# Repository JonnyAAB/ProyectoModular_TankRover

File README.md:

# ProyectoModular_TankRover
Este es un repositorio de un proyecto que ya está avanzado

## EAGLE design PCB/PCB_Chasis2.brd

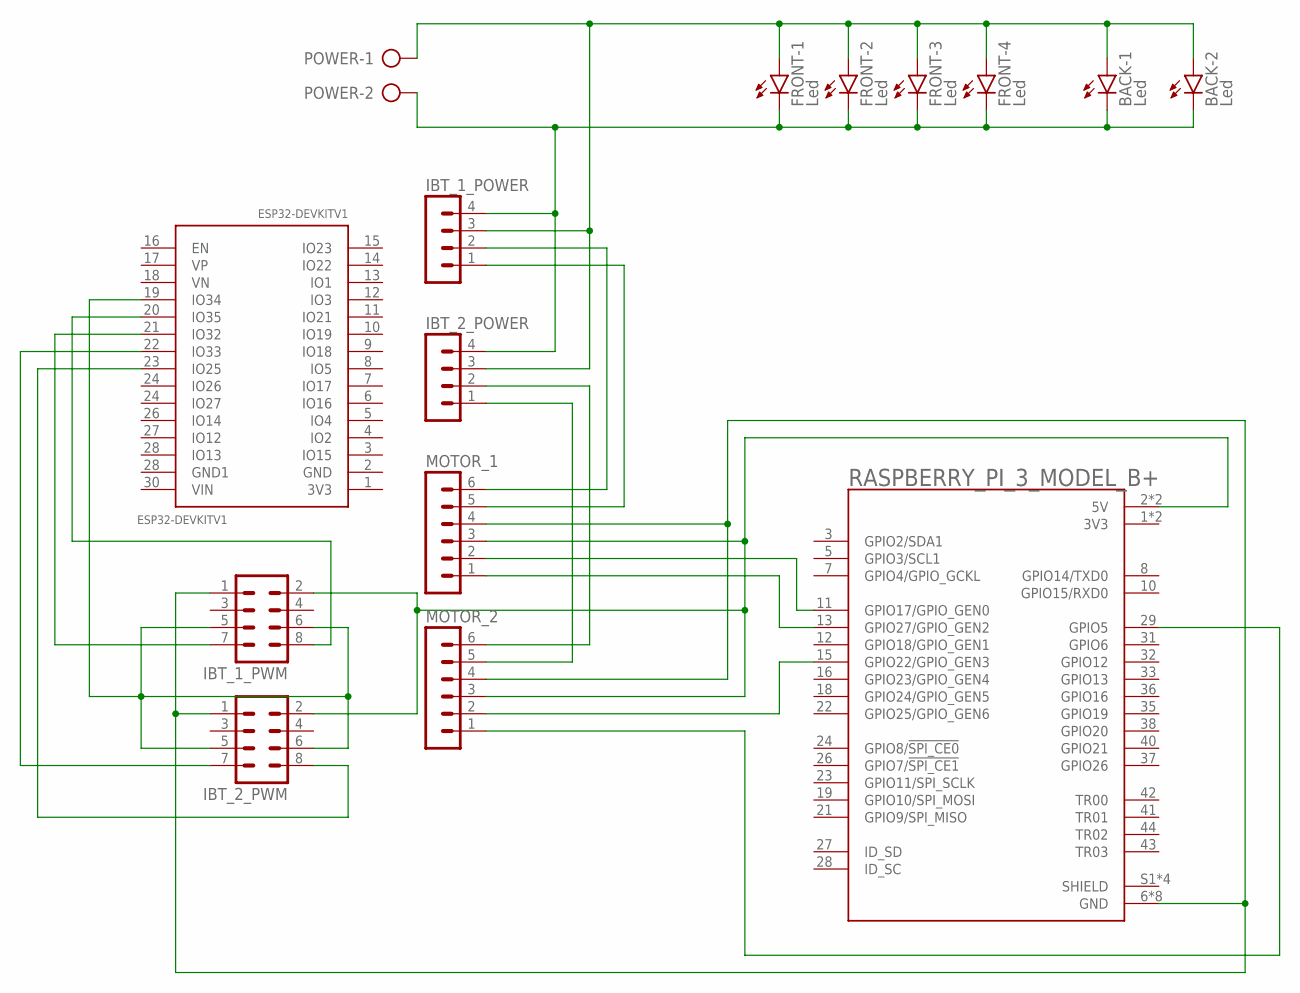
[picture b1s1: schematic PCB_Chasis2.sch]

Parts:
BACK: Led; LZR182
ESP32-DEVKITV1: ESP32DEVKITV1; ESP32-DEVKITV1
FRONT: Led; LZR184
IBT_1_POWER, IBT_2_POWER: MA04-1
IBT_1_PWM, IBT_2_PWM: MA04-2
MOTOR_1, MOTOR_2: MA06-1
POWER: AK500/2-H
RASPBERRY_PI_3_MODEL_B+: RASPBERRY_PI_3_MODEL_B+; MODULE_RASPBERRY_PI_3_MODEL_B+

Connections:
3V3: RASPBERRY_PI_3_MODEL_B+.1 (3V3), RASPBERRY_PI_3_MODEL_B+.17 (3V3)
unnamed: BACK.A1 (A), BACK.A2 (A), FRONT.A1 (A), FRONT.A2 (A), FRONT.A3 (A), FRONT.A4 (A), IBT_1_POWER.3, IBT_2_POWER.3, POWER.1
unnamed: BACK.K1 (C), BACK.K2 (C), FRONT.K1 (C), FRONT.K2 (C), FRONT.K3 (C), FRONT.K4 (C), IBT_1_POWER.4, IBT_2_POWER.4, POWER.2
unnamed: IBT_1_POWER.2, MOTOR_1.6
unnamed: IBT_1_POWER.1, MOTOR_1.5
unnamed: IBT_2_POWER.2, MOTOR_2.6
unnamed: IBT_2_POWER.1, MOTOR_2.5
unnamed: ESP32-DEVKITV1.19 (IO34), IBT_1_PWM.5, IBT_1_PWM.6, IBT_2_PWM.5, IBT_2_PWM.6
unnamed: IBT_1_PWM.2, IBT_2_PWM.2, MOTOR_1.3, MOTOR_2.3, RASPBERRY_PI_3_MODEL_B+.2 (5V), RASPBERRY_PI_3_MODEL_B+.4 (5V)
unnamed: MOTOR_1.2, RASPBERRY_PI_3_MODEL_B+.11 (GPIO17/GPIO_GEN0)
unnamed: MOTOR_1.1, RASPBERRY_PI_3_MODEL_B+.13 (GPIO27/GPIO_GEN2)
unnamed: MOTOR_2.2, RASPBERRY_PI_3_MODEL_B+.15 (GPIO22/GPIO_GEN3)
unnamed: MOTOR_2.1, RASPBERRY_PI_3_MODEL_B+.29 (GPIO5)
unnamed: IBT_1_PWM.1, IBT_2_PWM.1, MOTOR_1.4, MOTOR_2.4, RASPBERRY_PI_3_MODEL_B+.6 (GND), RASPBERRY_PI_3_MODEL_B+.9 (GND), RASPBERRY_PI_3_MODEL_B+.14 (GND), RASPBERRY_PI_3_MODEL_B+.20 (GND), RASPBERRY_PI_3_MODEL_B+.25 (GND), RASPBERRY_PI_3_MODEL_B+.30 (GND), RASPBERRY_PI_3_MODEL_B+.34 (GND), RASPBERRY_PI_3_MODEL_B+.39 (GND)
unnamed: ESP32-DEVKITV1.20 (IO35), IBT_1_PWM.8
unnamed: ESP32-DEVKITV1.21 (IO32), IBT_1_PWM.7
unnamed: ESP32-DEVKITV1.22 (IO33), IBT_2_PWM.7
unnamed: ESP32-DEVKITV1.23 (IO25), IBT_2_PWM.8
SHIELD: RASPBERRY_PI_3_MODEL_B+.S1 (SHIELD), RASPBERRY_PI_3_MODEL_B+.S2 (SHIELD), RASPBERRY_PI_3_MODEL_B+.S3 (SHIELD), RASPBERRY_PI_3_MODEL_B+.S4 (SHIELD)

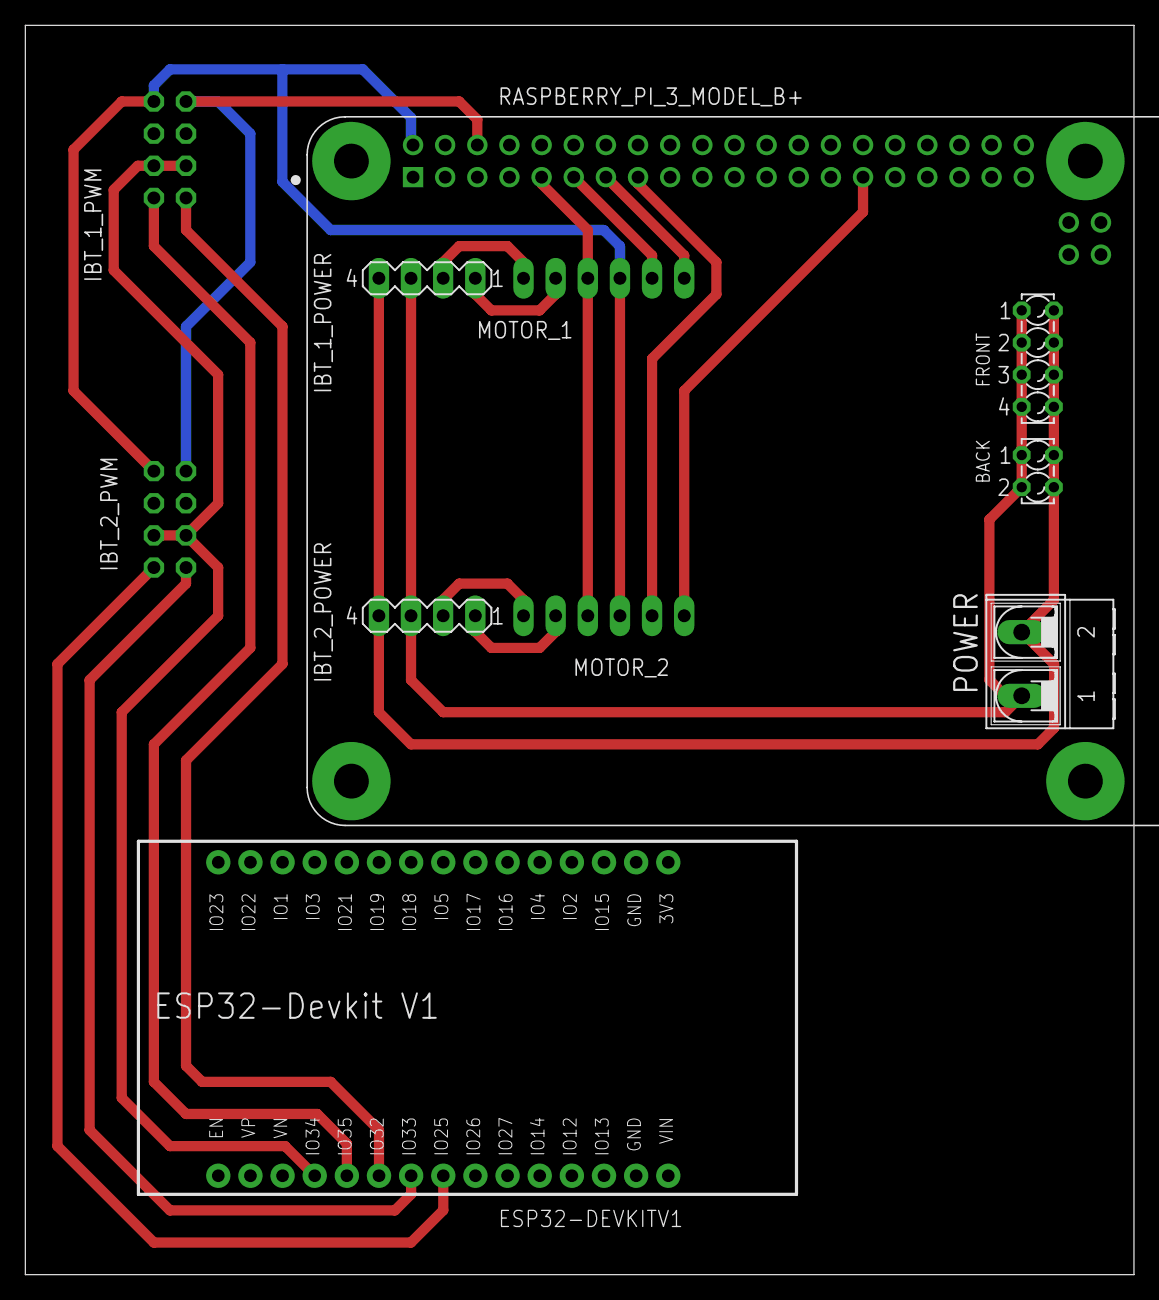
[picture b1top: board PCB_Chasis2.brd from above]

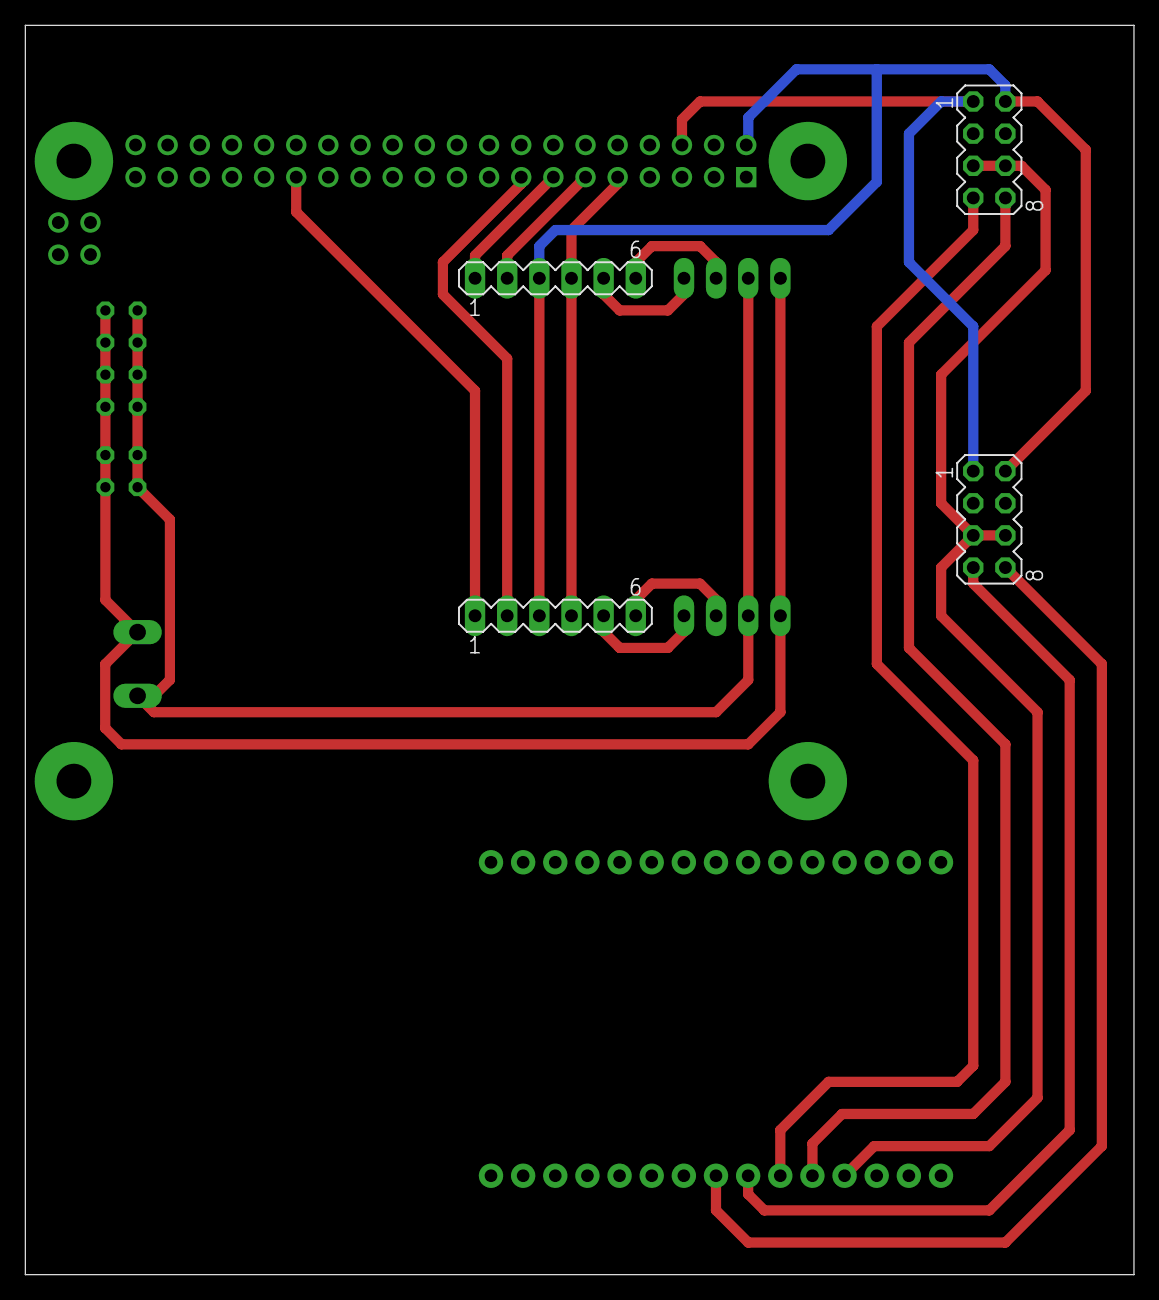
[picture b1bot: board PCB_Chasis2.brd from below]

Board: 2 copper layers, 87.6 x 98.7 mm, 11 parts (4 on the bottom side), 19 nets.

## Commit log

2023-10-07 Primer Commit
2023-10-07 Agregando comentarios
2023-10-07 Realizando Pruebas en Prueba.py
2023-10-07 Finalización de archivo de prueba
2023-10-08 Creacion PruebaMotorEncoder
2023-10-08 Creacion PruebaSensorCorriente
2023-10-10 Agregando un tercer PWM para R_EN y L_EN del driver que controla los motores
2023-10-14 Creando PruebaMotor, modificando PruebaMotorEncoder
2023-10-14 Añadiendo comentarios de pines para control del motor
2023-10-14 Corrijiendo comentarios xD
2023-10-14 Añadiendo una prueba y comentarios
2023-10-14 Añadiendo pruea del motor a PruebaEncoderJean
2023-10-14 No se que era el error pero creo que ya está
2023-10-14 Reestructura del codigo PruebaEncoderJean
2023-10-14 Mas cambios a PruebaEncoderJean
2023-10-14 Modificacion a la funcion
2023-10-14 Completando PruebaMotorEncoder en PrueaEncoderJean
2023-10-14 Completando completado PruebaMotorEncoder
2023-10-14 Terminando el control y añadiendo primeras pruebas
2023-10-14 Terminando Control y viendo forma de graficar
2023-10-14 Generando forma de leer plots
2023-10-15 Probando el plot en la rasperi
2023-10-15 Debe de haber una mejor forma de plotear :v
2023-10-15 Muestra de graficas en PDMotorEncoder
2023-10-15 Generando graficas de Posicion y accion de control
2023-10-15 Haciendo pruebas y agregando graficas
2023-10-15 Pruebas de Plot en distintas partes
2023-10-15 Añadiendo comentarios y optimizando PDMotorEncoder
2023-10-15 Organizando las pruebas en una carpeta
2023-10-15 Organizando por tipo de pruebas
2023-10-15 Creacion de carpeta para traajar con blutu
2023-10-21 Añadiendo codigo para prueba de blutu
2023-10-21 Cambiando de blutu a servidor local
2023-10-21 Configuracion server Rasp
2023-10-21 Configuracion Servidor Lap
2023-10-21 Añadiendo envio de datos por json
2023-10-21 Completando la pruea por red local B)
2023-10-21 "Completando la prueba coneccion desde la lap"
2023-10-21 Termino de la coneccion con control
2023-10-21 Termino de coneccion con rasp
2023-10-21 Cambio de nombres y organizacion
2023-10-21 Programa para conectar la rasp a una compu
2023-10-21 Agregando comentarios de uso
2023-10-21 Termino de conexiones Rasp
2023-10-21 Agregando mas comentarios xD
2023-10-21 Primeras pruebas
2023-10-21 Cambios en la conexion de lap
2023-10-21 Error con tabs
2023-10-21 Prueba 2 Coneccion
2023-10-21 Cambiando logica saturacion
2023-10-21 Termino del programa B)
2023-10-21 Cambio de nombre para mejor acceso
2023-10-21 MOdificando valor de saturacion
2023-10-21 Prueba de envio de listas
2023-10-22 Cambio nombre carpeta y prueba de mandar listas
2023-10-22 Empezando pruebas de mandar listas
2023-10-22 Prueba1 de envio de graficas
2023-10-22 Prueba 2 de envio de graficas
2023-10-24 Añadiendo comentarios y modificando logica de i en lap
2023-10-27 Cambios en la ip por configuración
2023-10-27 Primer prueba de conexion control xbox xD
2023-10-28 Mapeando el control de xbox prueba de funciones
2023-10-28 Primera prueba de carro controlado por mando
2023-10-28 Prueba 2 de control carro por mando
2023-10-28 saeas
2023-10-28 Corrigiendo logica de botones y control
2023-10-28 Arreglando cosos y terminado la prueba
2023-10-28 Primera prueba de lectura de ambos encoders
2023-10-28 Segunda prueba de lectura ambos encoders
2023-10-28 Cambios ip
2023-10-28 Fallo en el control
2023-10-28 Corrigiendo comentarios
2023-10-28 Cambiando prueba PruebaMotorEncoder para lectura de ambos encoder
2023-10-28 Terminando pruebas de lectura de ambos encoder y control en la principal de Rasp
2023-11-06 Pruebas implementacion conexion serial rasp/RaspESP32
2023-11-07 Completando Prueba de conexion seial esp32 con la rasp
2023-11-07 Realizando pruebas en la esp32
2023-11-07 Organizando las carpetas y eliminando archivos extra
2023-11-09 Primera prueba control Rasp/ESP32
2023-11-09 Primeras Pruebas de control Rasp/ESP32
2023-11-09 Modificacion de control con la ESP32 y Rasp
2023-11-09 Eliminacion de archivo RaspESP32ConeccionControl
2023-11-09 Cambio en el codigo de la ESP32
2023-11-09 Correcion de errores en el código ESP32RaspConeccionControl, finalizando pruebas
2023-11-09 Finalizacion del control lineal de los motores con la ESP32/Rasp
2023-11-09 Creacion de codigo para el modelo diferencial y V1 de la PCB
2024-04-04 Copia inicial del repositorio, modificaciones menores
2024-04-06 Agregando control individual y agregando graficas individuales
2024-04-23 Mejoras en lectura encoder
2024-04-24 Configuraciones de parametros
2024-04-24 Modificaciones en pc
2024-04-27 Añadiendo el codigo de la ESP32 en la carpeta ESP32Codigo
2024-04-28 Cambiando configuraciones
2024-05-02 Agregando archivos para el control cinematico (aun por hacer pruebas)
2024-05-02 Modificacion del programa para la ESP32
2024-05-04 Modificacion del codigo de la ESP32, y añadir comentarios
2024-05-04 Ultimos cambios en la esp32 y la rasp
2024-05-04 Cambios de prueba
2024-05-04 Codigo de la ESP32Codigo instaurado en la ESP32
2024-05-05 Actualizar Control_cinematico.py
2024-05-05 Cambios en el codigo de la ESP32. Funciona
2024-05-05 Cambios en el codigo de control, ya funciona
2024-05-05 Agregamos las pruebas del control cinematico
2024-05-06 Conversion encoder distancia y empezamos pruebas de Odometria
2024-05-06 Movimiento de carpetas para mejor organizacion
2024-05-06 Empezando con la escritura del tipo Diferencial
2024-05-06 Posible estimacion de pose, falta adecuarlo a la rasp
2024-05-07 Agregando nPID con simulación tanto en MATLAB como en Python
2024-05-07 Simulación que funciona en python
2024-05-07 Añadimos el control neuronal
2024-05-07 Cambiando extension a MatlabControl.m
2024-05-07 Clonacion master de Jonny
2024-05-07 Eliminando txt innecesarios
2024-05-07 Mejorando animacion e intento de rectangulo xD
2024-05-08 Primera version del nPID implementado en el robot real
2024-05-08 Ya no muevan naaaaaaaaaa
